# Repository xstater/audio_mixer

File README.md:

# audio_mixer
OPA1671 Audio Mixer

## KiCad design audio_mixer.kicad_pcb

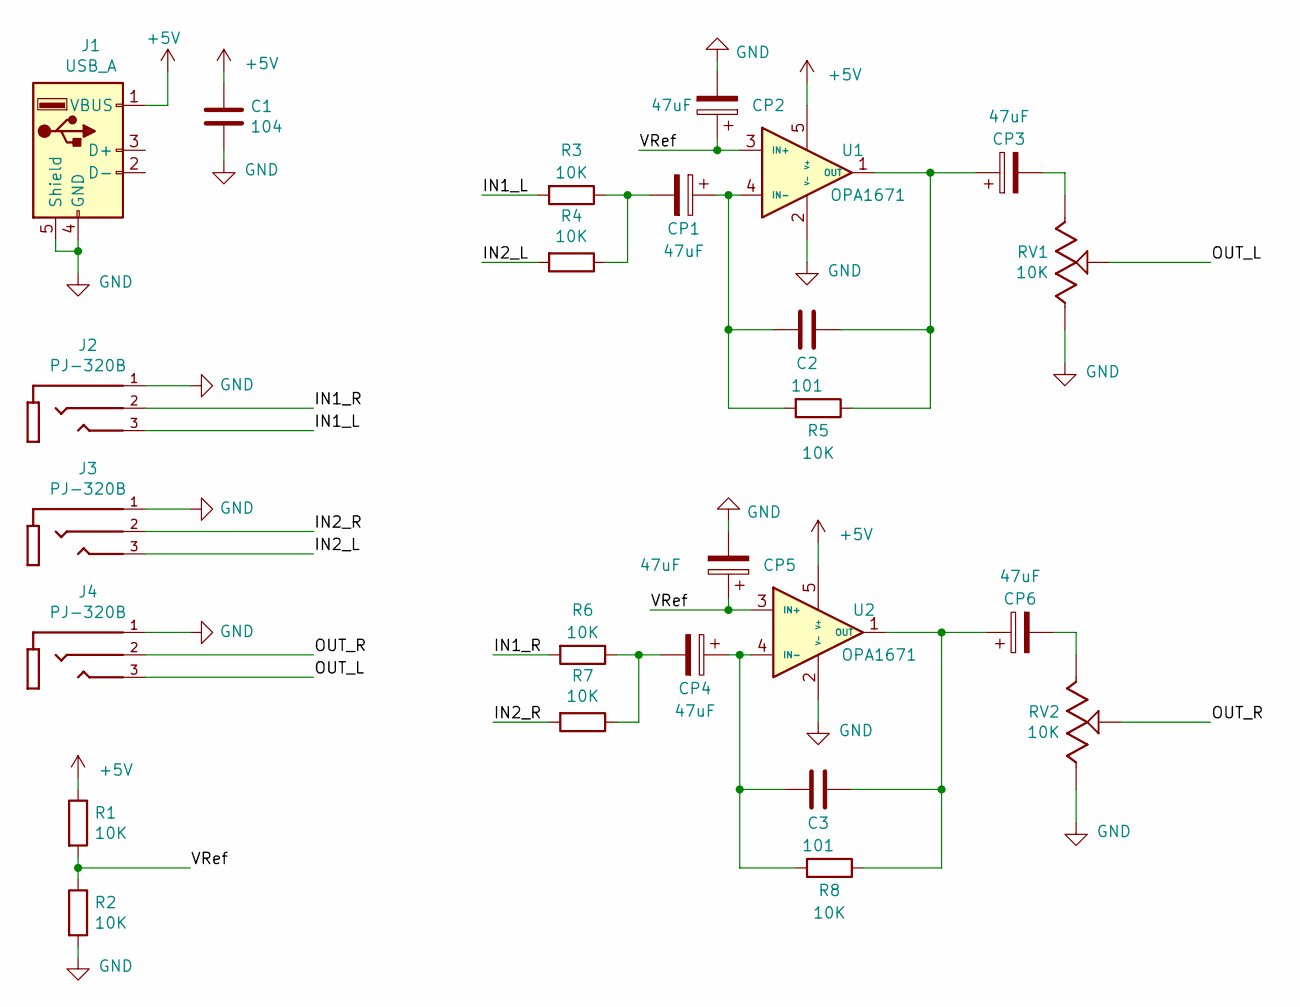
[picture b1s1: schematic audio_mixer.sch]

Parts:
C1: 104; C_0805_2012Metric
C2, C3: 101; C_0805_2012Metric
CP1, CP2, CP3, CP4, CP5, CP6: 47uF; CP_Radial_D8.0mm_P3.50mm
J1: USB_A; USB_A_CONNFLY_DS1095-WNR0
J2, J3, J4: PJ-320B; BOOMELE_PJ-320B
R1, R2, R3, R4, R5, R6, R7, R8: 10K; R_0805_2012Metric
RV1, RV2: 10K; TRIM_3296-W; PARTREV 08/19
U1, U2: OPA1671; SOT95P280X145-5N

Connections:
+5V: C1.1, J1.1 (VBUS), R1.1, U1.5 (V+), U2.5 (V+)
/IN1_L: J2.3, R3.2
/IN1_R: J2.2, R6.2
/IN2_L: J3.3, R4.2
/IN2_R: J3.2, R7.2
/OUT_L: J4.3, RV1.2
/OUT_R: J4.2, RV2.2
/VRef: CP2.1, CP5.1, R1.2, R2.1, U1.3 (IN+), U2.3 (IN+)
GND: C1.2, CP2.2, CP5.2, J1.4 (GND), J1.5 (Shield), J2.1, J3.1, J4.1, R2.2, RV1.1, RV2.1, U1.2 (V-), U2.2 (V-)
unnamed: C2.1, CP3.1, R5.1, U1.1 (OUT)
unnamed: C2.2, CP1.1, R5.2, U1.4 (IN-)
unnamed: C3.1, CP6.1, R8.1, U2.1 (OUT)
unnamed: C3.2, CP4.1, R8.2, U2.4 (IN-)
unnamed: CP1.2, R3.1, R4.1
unnamed: CP3.2, RV1.3
unnamed: CP4.2, R6.1, R7.1
unnamed: CP6.2, RV2.3

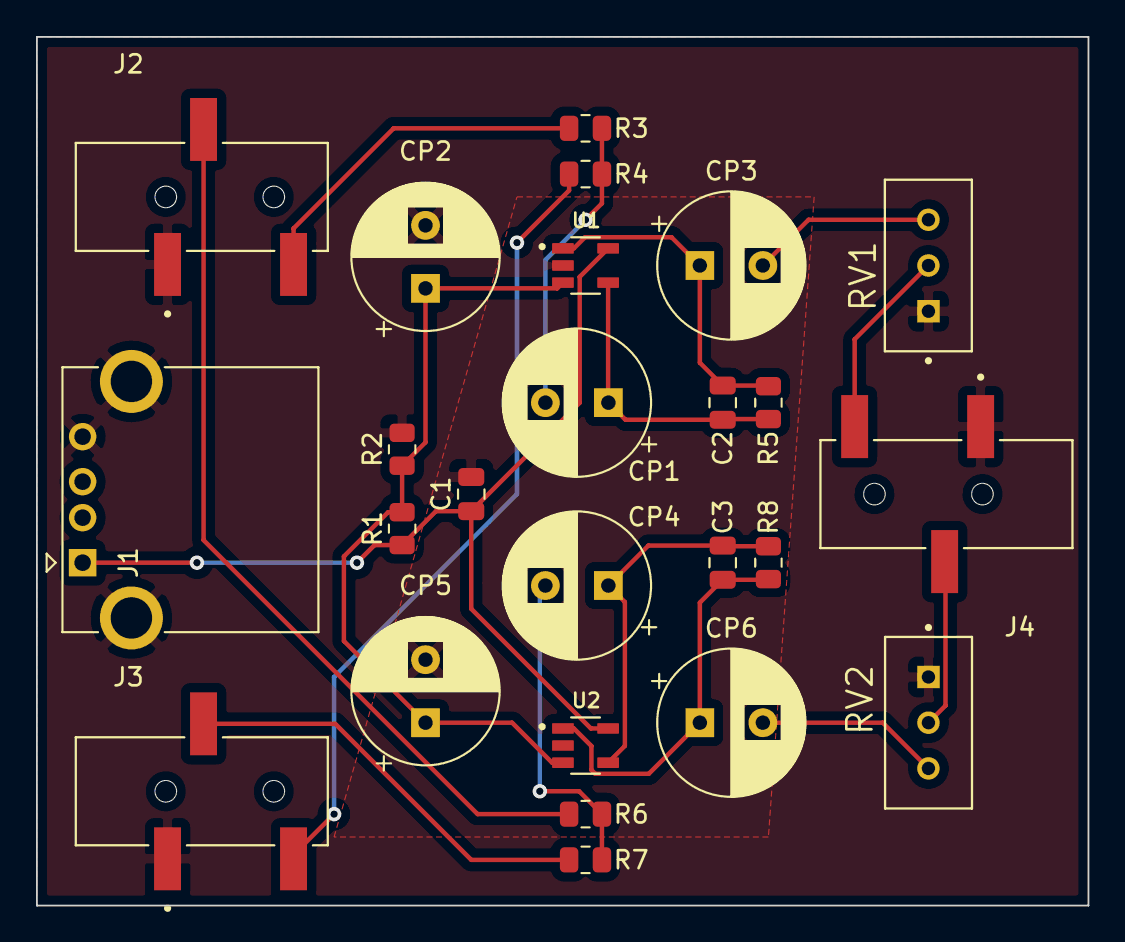
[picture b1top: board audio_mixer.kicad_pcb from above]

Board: 2 copper layers, 58.4 x 48.3 mm, 25 parts (0 on the bottom side), 17 nets.

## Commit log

2021-11-08 add new ignoring item
2021-11-08 init commit
